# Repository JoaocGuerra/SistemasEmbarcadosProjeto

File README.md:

# Sistemas Embarcados - 2021.2

#### Monitoramento do de temperatura de humidade por meio de sensores

### 1 - Descrição do projeto:

A agricultura familiar representa um contingente de 77% dos estabelecimentos
agrícolas do país. Esse trabalho desempenhado por essas famílias necessita do uso
de água para irrigação, sendo cada vez mais dependente da chamada agricultura de
precisão, em que dispositivos analisam de maneira inteligente as condições da lavoura no 
que diz respeito a temperatura e humidade controlando o tempo e a quantidade de água necessária 
para o processo de irrigação. Pensando nisso, visamos desenvolver um sistema embarcado capaz de sanar 
essas necessidades.

### 2 - Objetivos

  Geral
  
Nosso objetivo é desenvolver uma infraestrutura focada na interface com o usuário,
facilitando o acompanhamento da lavoura, sendo utilizados dispositivos de baixo
custo, permitindo a utilização desde o agricultor mais simples até os grandes
produtores.
  
  Especificos
 
Em relação a interface com o usuário, pensamos em fazer uma aplicação web
utilizando JavaScript onde serão dispostos os dados que os dispositivos
irão capturar.

Falando um pouco mais a estrutura de Hardware, utilizaremos o Sensor DTH, para
capturar os dados que seriam enviados para o ESP8266 de posse desses dados o ESP enviaria essas informações 
para uma interface gráfica onde esses dados poderiam ser analisados, armazenados
ou processados de forma a resolver algum problema relacionado ao monitoramento da 
temperatura e e humidade na agricultura.

### 3 - Resumo das arquiteturas
  
  1.  Hardware

	- ESP8266 (Caso seja necessário enviar dados por internet)
	- Sensor de Temperatura e Humidade DHT11
	- Mini protoboard
	- Jumpers

  2.  Firmaware e/ou Software/App 
  
	- Utilizaremos um sistema de tempo real (RTOS) para implementar a logica do firmware

### 4 - Resumo dos Resultados

#### 4.1 Documentação e Diagrama de Blocos

##### Diagrama de Blocos do Hardware  

##### Design do Sistema em Blocos

#### Diagrama de Blocos do Firmware

#### Diagrama de Blocos da Aplicação Web

> [Relatório Final](https://docs.google.com/document/d/1OH0ySzCCkVx8VMb1BBHpwzDGqj-EqATqLdINgi41xL8/edit?usp=sharing)

#### 4.2 Conceito parcial de Esquemático 

#### 4.3 Conceito parcial de Modelo 3D

#### Para o 3D e PCB foram criados dois modelos: 

1. Todos os fios na camada button porém o ESP8266 também ficou na parte de baixo da placa <br>
- [Fusion 360 Online 3D Protótipo 1](https://a360.co/3JpDviy)

2. Todos os componentes na camada superior porem um dos fios ficou fizemos ajustes na coneção com o ESP8266 <br>
- [Fusion 360 Online 3D Protótipo 2](https://a360.co/3q3f3vH)

#### Aplicação desenvolvida do zero independende do ESP8266

Conforme apresentado no design ou arquitetura do sistema foi planejado a criaçao de um sistema com interface Web para mostrar ao usuário os dados coletados pelo sensor, essa aplicação pode ser acessada por esse link: 

:point_right: [Site da Aplicação](https://embedded-dashboad.netlify.app/)

A aplicação faz um request no banco de dados a cada 5 segundos e atualiza a interface em tempo real, sem o usuário precisar pressionar f5 ou dar um refresh na pagina. Por questões de economia de banda o ESP-8266 não está ligado diariamente por isso os dados podem estar fixos. No entanto basta ligar o sensor, assim o que ESP8266 enviar os dados a aplicação é atualizada com as novas leituras. 

### Vídeo da Apresentação 

[
](https://www.youtube.com/watch?v=Y-9e6XvYydM)

### 5 - Grupo

* João Carlos Guerra de Abreu
* Lucas Matheus Torres Costa
* Rafael Figueredo Guimarães

### 6 - Instituição

* Instituto Federal da Paraíba - IFPB
* Campus Campina Grande

### Docente responsável
* Alexandre Sales Vasconcelos

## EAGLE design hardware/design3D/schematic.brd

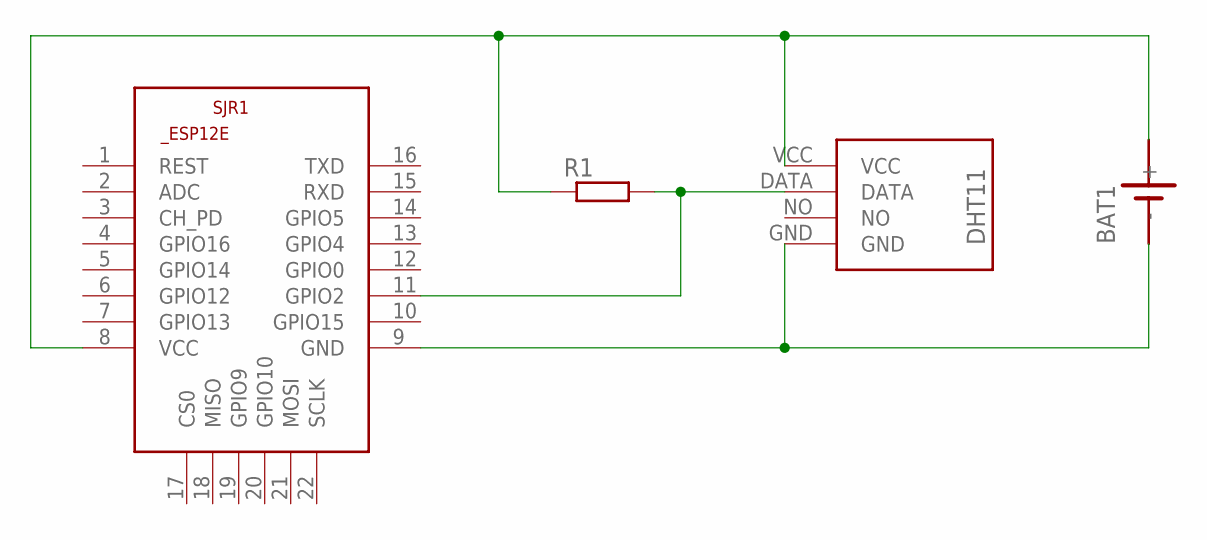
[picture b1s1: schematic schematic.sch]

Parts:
BAT1: SN2032
R1: 10 kΩ; 0207/10
SJR1: ESP8266-12EESP12E; ESP8266-ESP12E
U$2: DHT11

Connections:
unnamed: BAT1.+, R1.1, SJR1.8 (VCC), U$2.VCC
unnamed: BAT1.-, SJR1.9 (GND), U$2.GND
unnamed: R1.2, SJR1.11 (GPIO2), U$2.DATA

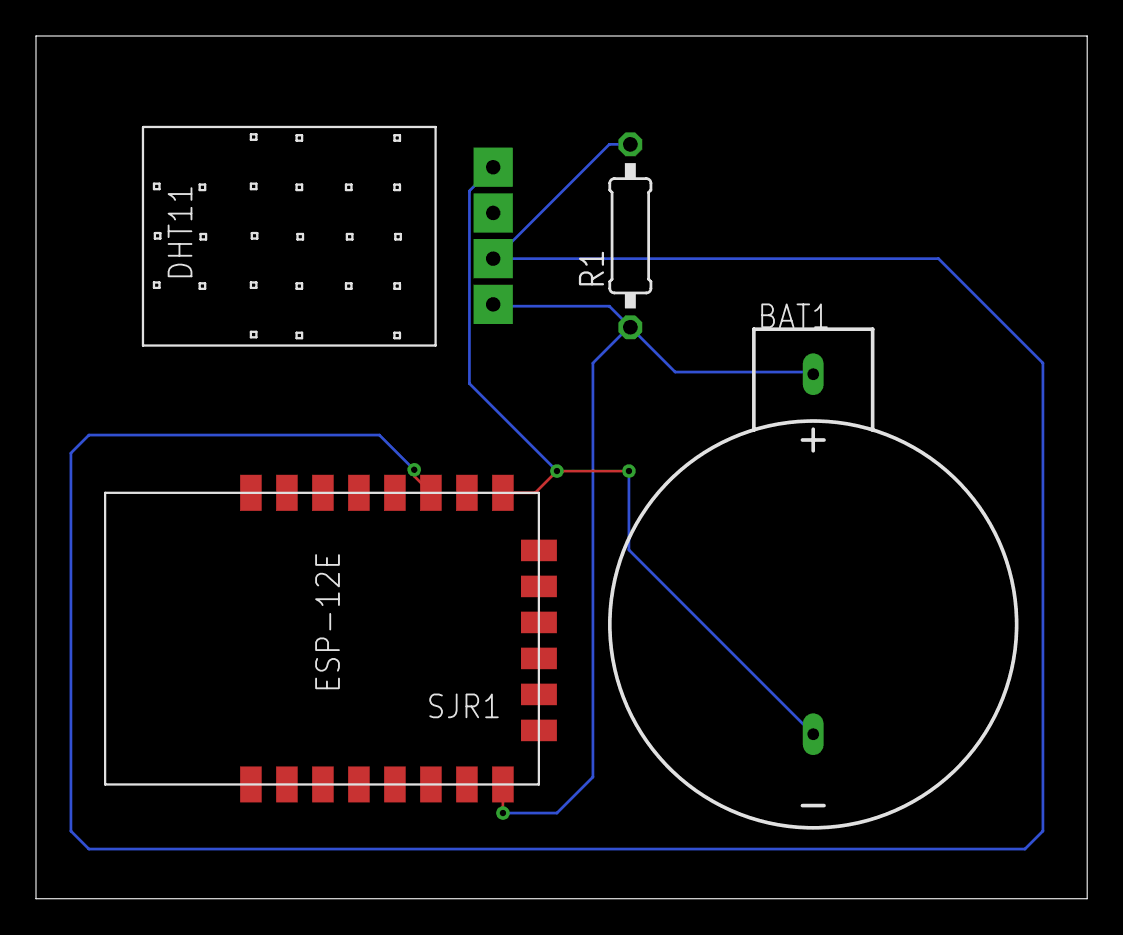
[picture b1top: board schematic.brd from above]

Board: 2 copper layers, 58.4 x 47.9 mm, 4 parts (0 on the bottom side), 3 nets.

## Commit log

2021-11-27 Adicionando a descrição sobre o dispositivo.
2021-12-01 Deletando para adicionar arquivo atualizado.
2021-12-01 Desscrição do projeto atualizada.
2022-02-21 Initialize directories
2022-02-21 add parcial presentation
2022-03-17 Add descrição do projeto atualizada
2022-03-17 Designs desenvolvidos no eagle e fusion 360
2022-03-20 add firmware
2022-03-20 Adiciona novos arquivos ao repositório
    - Adiciona o código do dashboard
    - Adiciona o relatório final
    - Adiciona a descrição do hardware
2022-03-20 Removing package that it's not working
2022-03-20 Atualiza app
    - Adiciona codigo da aplicação web
2022-03-20 Adiciona fluxograma do firmaware
2022-03-20 Adiciona fluxograma da aplicação web
2022-03-22 Adiciona apresentação final do projeto
